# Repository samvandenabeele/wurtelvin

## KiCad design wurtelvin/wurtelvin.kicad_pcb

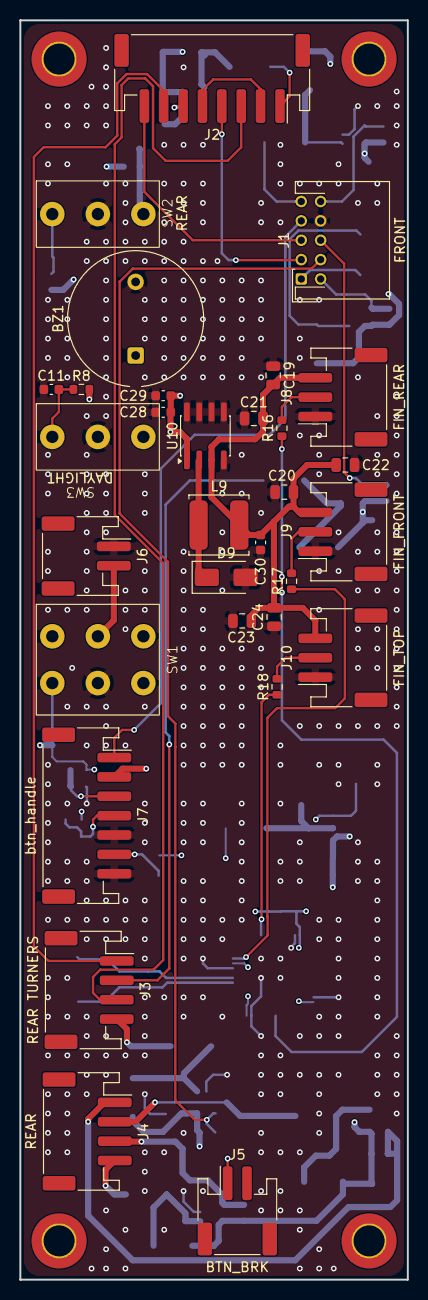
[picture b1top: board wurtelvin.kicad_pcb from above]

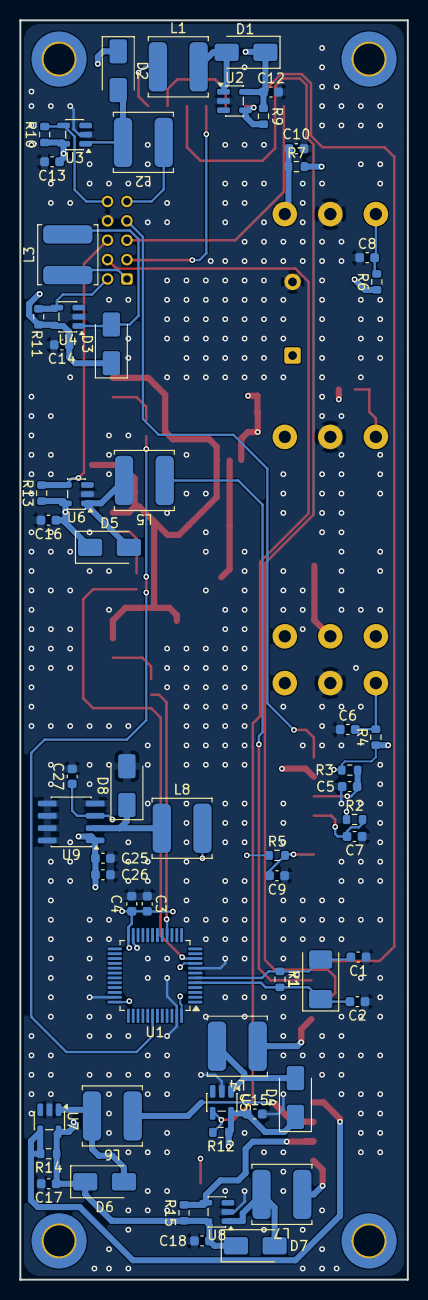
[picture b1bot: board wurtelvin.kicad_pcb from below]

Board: 4 copper layers, 40.0 x 130.0 mm, 91 parts (60 on the bottom side), 49 nets.

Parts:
BZ1: Buzzer; Indicator_PUI_AI-1440-TWT-24V-2-R
C1, C2: 20pF; C_0603_1608Metric
C3: 1uF; C_0603_1608Metric
C4: 10nF; C_0603_1608Metric
C5, C6, C7, C8, C9, C10, C11: 0.1uF; C_0603_1608Metric
C12, C13, C14, C15, C16, C17, C18: 22uF; C_0603_1608Metric
C19, C20, C21, C22, C23, C24: 330uF; C_0805_2012Metric
C25, C28: 470uF; C_0603_1608Metric
C26, C29: 105uF; C_0603_1608Metric
C27: 330uF; C_0603_1608Metric
C30: 180uF; C_0603_1608Metric
D1, D2, D3, D4, D5, D6, D7: SS14; D_SMA
D8, D9: SS32; D_SMA
J1: FRONT; JST_PHD_S10B-PHDSS_2x05_P2.00mm_Horizontal
J2: MIRRORS; JST_PH_S8B-PH-SM4-TB_1x08-1MP_P2.00mm_Horizontal
J3: REAR TURNERS; JST_PH_S4B-PH-SM4-TB_1x04-1MP_P2.00mm_Horizontal
J4: REAR; JST_PH_S4B-PH-SM4-TB_1x04-1MP_P2.00mm_Horizontal
J5: BTN_BRK; JST_PH_S2B-PH-SM4-TB_1x02-1MP_P2.00mm_Horizontal
J6: BATT; JST_PH_S2B-PH-SM4-TB_1x02-1MP_P2.00mm_Horizontal
J7: btn_handle; JST_PH_S7B-PH-SM4-TB_1x07-1MP_P2.00mm_Horizontal
J8: FIN_REAR; JST_PH_S3B-PH-SM4-TB_1x03-1MP_P2.00mm_Horizontal
J9: FIN_FRONT; JST_PH_S3B-PH-SM4-TB_1x03-1MP_P2.00mm_Horizontal
J10: FIN_TOP; JST_PH_S3B-PH-SM4-TB_1x03-1MP_P2.00mm_Horizontal
L1, L2, L3, L4, L5, L6, L7: 45uH; L_TDK_VLS6045EX_VLS6045AF
L8: 47uH; L_TDK_VLS6045EX_VLS6045AF
L9: 68uH; L_TDK_VLS6045EX_VLS6045AF
R1: 1M; R_0603_1608Metric
R2, R3, R5: 4.7K; R_0603_1608Metric
R4, R6, R7, R8: 4.7k; R_0603_1608Metric
R9, R12, R13, R14, R15: 0.3; R_0603_1608Metric
R10, R11: R; R_0603_1608Metric
R16, R17, R18: 300; R_0603_1608Metric
SW1: SW_DPDT_x2; ANT_2x3
SW2: REAR; ANT_1x3
SW3: DAYLIGHT; ANT_1x3
U1: STM32F103C8Tx; LQFP-48_7x7mm_P0.5mm
U2, U3, U4, U5, U6, U7, U8: AL8860WT; TSOT-23-5
U9: XL1509-3.3; SOIC-8_3.9x4.9mm_P1.27mm
U10: XL1509-5.0; SOIC-8_3.9x4.9mm_P1.27mm
Y1: 8MHz; Crystal_SMD_Abracon_ABM3-2Pin_5.0x3.2mm

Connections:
+3V3: C3.1, C4.1, C27.1, J5.1, L8.2, R2.1, R3.1, R4.1, R5.1, R6.1, R7.1, R8.1, U1.9 (VDDA), U1.24 (VDD), U1.36 (VDD), U1.48 (VDD), U9.3 (FB)
+5V: C19.2, C20.2, C21.2, C22.2, C23.2, C24.2, C30.1, J8.3, J9.3, J10.3, L9.2, U10.3 (FB)
+BATT: C12.1, C13.1, C14.1, C15.1, C16.1, C17.1, C18.1, C25.1, C26.1, C28.1, C29.1, D1.1 (K), D2.1 (K), D3.1 (K), D4.1 (K), D5.1 (K), D6.1 (K), D7.1 (K), J7.2, R9.1, R10.1, R11.1, R12.1, R13.1, R14.1, R15.1, SW1.1 (A), SW1.3 (C), U2.5 (VIN), U3.5 (VIN), U4.5 (VIN), U5.5 (VIN), U6.5 (VIN), U7.5 (VIN), U8.5 (VIN), U9.1 (VIN), U10.1 (VIN)
/BRK+: J4.3, R15.2, U8.4 (SET)
/BRK-: J4.4, L7.1
/BTN_BEAM: C9.2, J7.6, R5.2
/BTN_DIM: C6.2, R4.2, SW1.4 (A)
/BTN_DL: C11.2, R8.2, SW3.1 (A)
/BTN_REAR: C8.2, R6.2, SW2.1 (A)
/BTN_REAR_BLK: C10.2, R7.2, SW2.3 (C)
/BTN_TLL: C5.2, J7.3, R3.2
/BTN_TLR: C7.2, J7.4, R2.2
/DL+: J2.6, R9.2, U2.4 (SET)
/DL-: J2.1, L1.1
/FF_DATA: R17.1, U1.10 (PA0)
/FH+: J1.10, R10.2, U3.4 (SET)
/FH-: J1.9, L2.1
/FL+: J1.2, R11.2, U4.4 (SET)
/FL-: J1.1, L3.1
/FR_DATA: R16.1, U1.42 (PB6)
/FT_DATA: R18.1, U1.16 (PA6)
/HORN+: J1.7, J7.1
/OSC_IN: C2.2, R1.2, U1.5 (PD0), Y1.1
/OSC_OUT: C1.2, R1.1, U1.6 (PD1), Y1.2
/REAR+: J4.1, R14.2, U7.4 (SET)
/REAR-: J4.2, L6.1
/TLL+: J1.6, R13.2, U6.4 (SET)
/TLL-: J3.2, L5.1
/TLR+: J1.4, R12.2, U5.4 (SET)
/TLR-: J3.4, L4.1
GND: BZ1.2 (-), C1.1, C2.1, C3.2, C4.2, C5.1, C6.1, C7.1, C8.1, C9.1, C10.1, C11.1, C12.2, C13.2, C14.2, C15.2, C16.2, C17.2, C18.2, C19.1, C20.1, C21.1, C22.1, C23.1, C24.1, C25.2, C26.2, C27.2, C28.2, C29.2, C30.2, D8.2 (A), D9.2 (A), J1.8, J6.1, J7.5, J7.7, J8.1, J9.1, J10.1, SW1.5 (B), SW2.2 (B), SW3.2 (B), U1.8 (VSSA), U1.23 (VSS), U1.35 (VSS), U1.47 (VSS), U2.2 (GND), U3.2 (GND), U4.2 (GND), U5.2 (GND), U6.2 (GND), U7.2 (GND), U8.2 (GND), U9.4 (~EN), U9.5 (GND), U9.6 (GND), U9.7 (GND), U9.8 (GND), U10.4 (~EN), U10.5 (GND), U10.6 (GND), U10.7 (GND), U10.8 (GND)
unnamed: D1.2 (A), L1.2, U2.1 (SW)
unnamed: D2.2 (A), L2.2, U3.1 (SW)
unnamed: D3.2 (A), L3.2, U4.1 (SW)
unnamed: D4.2 (A), L4.2, U5.1 (SW)
unnamed: D5.2 (A), L5.2, U6.1 (SW)
unnamed: D6.2 (A), L6.2, U7.1 (SW)
unnamed: D7.2 (A), L7.2, U8.1 (SW)
unnamed: D8.1 (K), L8.1, U9.2 (OUT)
unnamed: D9.1 (K), L9.1, U10.2 (OUT)
unnamed: J1.3, J2.4
unnamed: J1.5, J2.8
unnamed: J2.2, J2.5
unnamed: J2.3, J3.3
unnamed: J2.7, J3.1
unnamed: J6.2, SW1.2 (B)
unnamed: J8.2, R16.2
unnamed: J9.2, R17.2
unnamed: J10.2, R18.2
